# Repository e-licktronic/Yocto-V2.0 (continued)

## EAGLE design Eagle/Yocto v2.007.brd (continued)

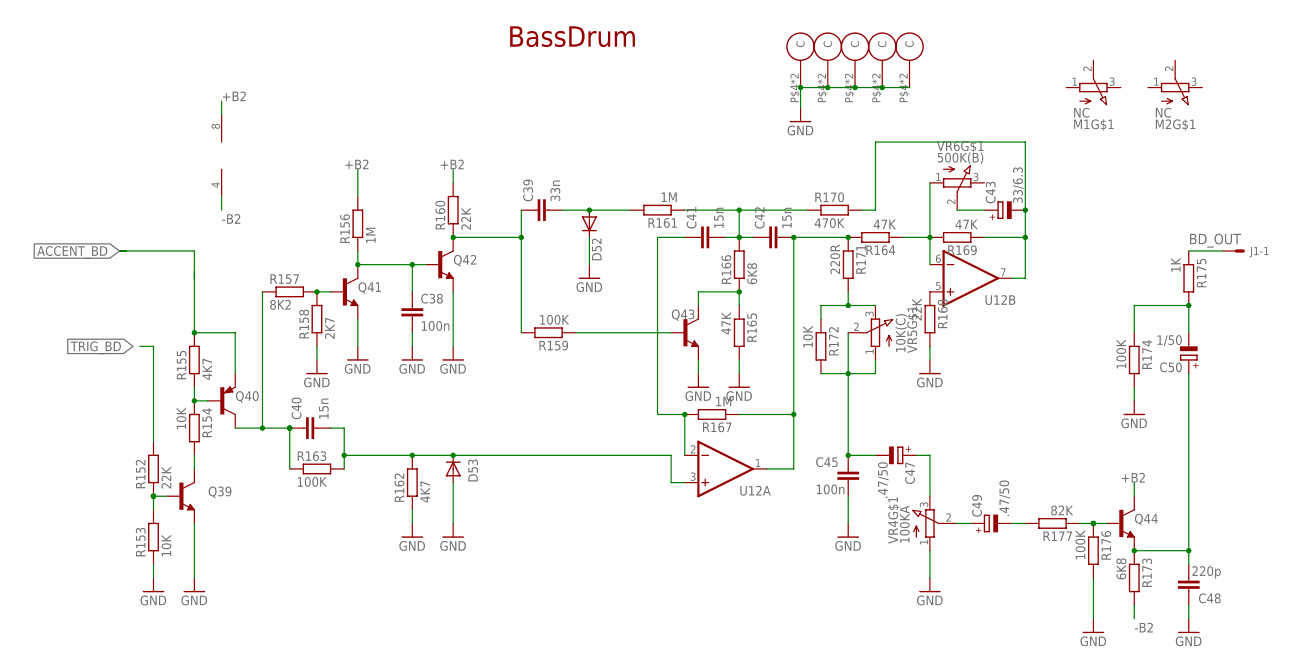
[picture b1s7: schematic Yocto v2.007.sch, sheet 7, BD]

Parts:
C38, C45: 100n; C050-025X075
C39: 33n; C050-025X075
C40, C41, C42: 15n; C050-025X075
C43: 33/6.3; E2,5-5
C47, C49: .47/50; E2,5-5
C48: 220p; C025-025X050
C50: 1/50; E2,5-5
D52, D53: 1N4148DO35-7; DO35-7
J1: 22-27-2041-04; 6410-04
M1, M2: NC; R0903N
Q39, Q41, Q42, Q43, Q44: 2SC945; TO-92-ECB-PERSO
Q40: 2SA733; TO-92-ECB-MARKED
R152: 22K; 0207/7
R153, R154: 10K; 0207/7
R155, R162: 4K7; 0207/5V
R156, R161, R167: 1M; 0207/5V
R157: 8K2; 0207/5V
R158: 2K7; 0207/5V
R159, R163, R174: 100K; 0207/5V
R160, R168: 22K; 0207/5V
R164: 47K; 0207/7
R165, R169: 47K; 0207/5V
R166, R173: 6K8; 0207/5V
R170: 470K; 0207/7
R171: 220R; 0207/5V
R172: 10K; 0207/5V
R175: 1K; 0207/5V
R176: 100K; 0207/7
R177: 82K; 0207/5V
U12: µPC4558CA; DIL08
VR4: 100KA; R0903N
VR5: 10K(C); R0903N
VR6: 500K(B); R0903N

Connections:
+B2: Q44.C, R156.2, R160.2, U12.8 (V+); also elsewhere on the board
-B2: R173.2, U12.4 (V-); also elsewhere on the board
ACCENT_BD: Q40.E, R155.2; also elsewhere on the board
BD_OUT: J1.1, R175.1
C1: C49.-, R177.2
GND: C38.2, C45.2, C48.1, D52.C, D53.A, M1.P$4 (C), M1.P$5 (C), M2.P$4 (C), M2.P$5 (C), Q39.E, Q41.E, Q42.E, Q43.E, R153.1, R158.1, R162.1, R165.2, R168.2, R174.2, R176.2, VR4.1 (A), VR4.P$4 (C), VR4.P$5 (C), VR5.P$4 (C), VR5.P$5 (C), VR6.P$4 (C), VR6.P$5 (C); also elsewhere on the board
unnamed: C38.1, Q41.C, Q42.B, R156.1
unnamed: Q40.B, R154.1, R155.1
unnamed: Q39.C, R154.2
unnamed: C39.1, Q42.C, R159.2, R160.1
unnamed: C40.1, Q40.C, R157.1, R163.1
unnamed: C40.2, D53.C, R162.2, R163.2, U12.3 (+IN)
unnamed: Q43.B, R159.1
unnamed: C41.2, C42.1, R161.1, R166.2, R170.1
unnamed: C41.1, R167.2, U12.2 (-IN)
unnamed: C42.2, R164.2, R167.1, R171.1, U12.1 (OUT)
unnamed: C45.1, C47.-, R172.2, VR5.1 (A), VR5.2 (S)
unnamed: R171.2, R172.1, VR5.3 (E)
unnamed: R164.1, R169.2, U12.6 (-IN), VR6.1 (A)
unnamed: C43.-, R169.1, R170.2, U12.7 (OUT)
unnamed: Q44.B, R176.1, R177.1
unnamed: C48.2, C50.+, Q44.E, R173.1
unnamed: C50.-, R174.1, R175.2
unnamed: C47.+, VR4.3 (E)
unnamed: C49.+, VR4.2 (S)
unnamed: C39.2, D52.A, R161.2
unnamed: C43.+, VR6.2 (S)
unnamed: R168.1, U12.5 (+IN)
unnamed: Q41.B, R157.2, R158.2
unnamed: Q43.C, R165.1, R166.1
unnamed: Q39.B, R152.1, R153.2
TRIG_BD: R152.2; also elsewhere on the board

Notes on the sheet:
BassDrum

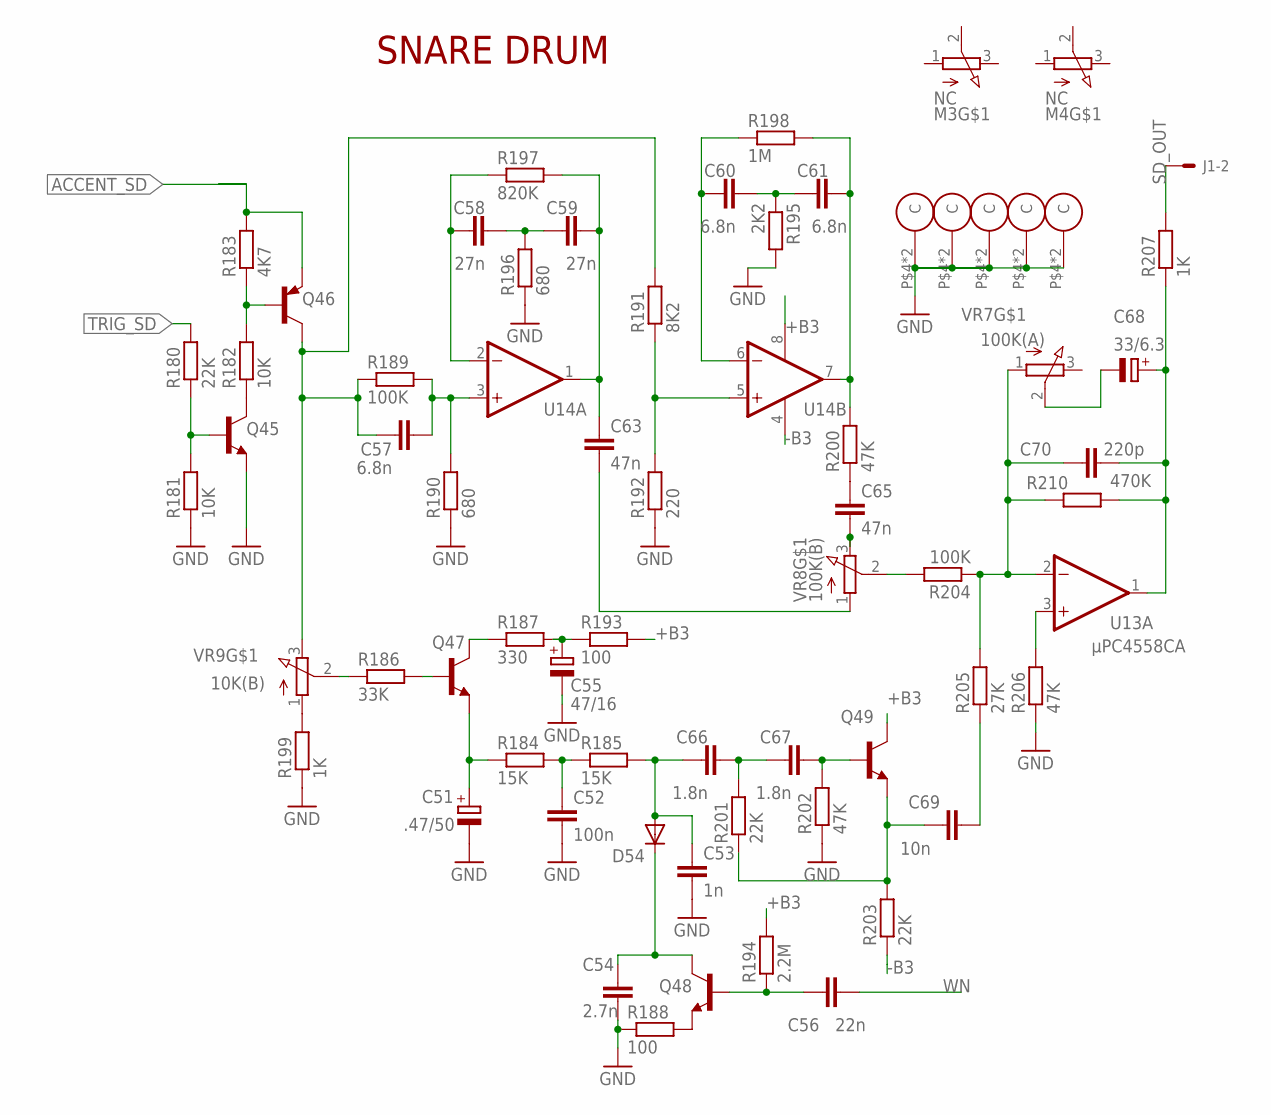
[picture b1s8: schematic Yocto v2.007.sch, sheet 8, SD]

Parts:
C51: .47/50; E2-5
C52: 100n; C050-025X075
C53: 1n; C050-025X075
C54: 2.7n; C050-025X075
C55: 47/16; E2-5
C56: 22n; C050-025X075
C57, C60, C61: 6.8n; C050-025X075
C58, C59: 27n; C050-025X075
C63, C65: 47n; C050-025X075
C66, C67: 1.8n; C050-025X075
C68: 33/6.3; E2-5
C69: 10n; C050-025X075
C70: 220p; C025-025X050
D54: 1N4148; DO35-7C
J1: 22-27-2041-04; 6410-04
M3, M4: NC; R0903N
Q45, Q47, Q48, Q49: 2SC945; TO-92-ECB-PERSO
Q46: 2SA733; TO-92-ECB-MARKED
R180, R201, R203: 22K; 0207/7
R181, R182: 10K; 0207/7
R183: 4K7; 0207/7
R184, R185: 15K; 0207/7
R186: 33K; 0207/7
R187: 330; 0207/7
R188, R193: 100; 0207/7
R189, R204: 100K; 0207/7
R190, R196: 680; 0207/7
R191: 8K2; 0207/7
R192: 220; 0207/7
R194: 2.2M; 0207/7
R195: 2K2; 0207/7
R197: 820K; 0207/7
R198: 1M; 0207/7
R199, R207: 1K; 0207/7
R200, R202, R206: 47K; 0207/7
R205: 27K; 0207/7
R210: 470K; 0207/7
U13, U14: µPC4558CA; DIL08
VR7: 100K(A); R0903N
VR8: 100K(B); R0903N
VR9: 10K(B); R0903N

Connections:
+B3: Q49.C, R193.2, R194.2, U14.8 (V+); also elsewhere on the board
-B3: R203.1, U14.4 (V-); also elsewhere on the board
ACCENT_SD: Q46.E, R183.2; also elsewhere on the board
GND: C51.-, C52.2, C53.2, C54.2, C55.-, M3.P$4 (C), M3.P$5 (C), M4.P$4 (C), M4.P$5 (C), Q45.E, R181.1, R188.1, R190.1, R192.1, R195.2, R196.1, R199.1, R202.1, R206.1, VR7.P$4 (C), VR7.P$5 (C), VR8.P$4 (C), VR8.P$5 (C), VR9.P$4 (C), VR9.P$5 (C); also elsewhere on the board
unnamed: Q45.B, R180.1, R181.2
unnamed: Q46.B, R182.2, R183.1
unnamed: Q45.C, R182.1
unnamed: C57.2, R189.2, R190.2, U14.3 (+IN)
unnamed: C57.1, Q46.C, R189.1, R191.2, VR9.3 (E)
unnamed: C58.1, R197.1, U14.2 (-IN)
unnamed: C59.2, C63.1, R197.2, U14.1 (OUT)
unnamed: C58.2, C59.1, R196.2
unnamed: C61.2, R198.2, R200.2, U14.7 (OUT)
unnamed: C60.2, C61.1, R195.1
unnamed: R191.1, R192.2, U14.5 (+IN)
unnamed: C63.2, VR8.1 (A)
unnamed: C65.1, R200.1
unnamed: R199.2, VR9.1 (A)
unnamed: C52.1, R184.2, R185.1
unnamed: R186.1, VR9.2 (S)
unnamed: Q47.B, R186.2
unnamed: Q47.C, R187.1
unnamed: C55.+, R187.2, R193.1
unnamed: C51.+, Q47.E, R184.1
unnamed: C53.1, C66.1, D54.A, R185.2
unnamed: C66.2, C67.1, R201.2
unnamed: C67.2, Q49.B, R202.2
unnamed: C69.1, Q49.E, R201.1, R203.2
unnamed: Q48.E, R188.2
unnamed: C54.1, D54.C, Q48.C
unnamed: C56.1, Q48.B, R194.1
unnamed: R204.2, VR8.2 (S)
unnamed: C70.1, R204.1, R205.2, R210.1, U13.2 (-IN), VR7.1 (A)
unnamed: C69.2, R205.1
unnamed: R206.2, U13.3 (+IN)
unnamed: C65.2, VR8.3 (E)
unnamed: C68.+, C70.2, R207.1, R210.2, U13.1 (OUT)
unnamed: C68.-, VR7.2 (S)
unnamed: C60.1, R198.1, U14.6 (-IN)
SD_OUT: J1.2, R207.2
TRIG_SD: R180.2; also elsewhere on the board
WN: C56.2; also elsewhere on the board

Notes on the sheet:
SNARE DRUM

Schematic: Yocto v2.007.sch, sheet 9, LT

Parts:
C71, C74, C77, C81: 47n; C050-025X075
C72: 39n; C050-025X075
C73: 6.8n; C050-025X075
C75: 18n; C050-025X075
C76: 56n; C050-025X075
C78: 12n; C050-025X075
C82: 33/6.3; E2-5
C83: 1n; C050-025X075
D55, D56: 1N4148; DO35-7C
D80, D81: 1N34; DO35-7C
J1: 22-27-2041-04; 6410-04
M5, M6: NC; R0903N
Q50, Q52: 2SC945; TO-92-ECB-PERSO
Q51: 2SA733; TO-92-ECB-MARKED
R211, R222, R223, R226: 22K; 0207/7
R212, R213: 10K; 0207/7
R214, R215, R219, R221, R225: 4K7; 0207/7
R216: 15K; 0207/7
R217: 3K3; 0207/7
R218: 2M2; 0207/7
R220, R227, R229: 33K; 0207/7
R224: 1K5; 0207/7
R228, R230: 820K; 0207/7
R231, R238: 1K; 0207/7
R232, R233: 100K; 0207/7
R234: 47K; 0207/7
R235: 470K; 0207/7
SW8: MSS42_SW_4PDT; MSS42_SW_SLIDE
U13, U15: µPC4558CA; DIL08
VR10: 100KA; R0903N
VR11: 500R; R0903N

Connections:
+B3: U13.8 (V+); also elsewhere on the board
+B4: R221.1, U15.8 (V+); also elsewhere on the board
-B3: U13.4 (V-); also elsewhere on the board
-B4: U15.4 (V-); also elsewhere on the board
ACCENT_LT: Q51.E, R214.2; also elsewhere on the board
GND: C72.2, C75.2, D56.A, M5.P$4 (C), M5.P$5 (C), M6.P$4 (C), M6.P$5 (C), Q50.E, Q52.E, R212.1, R215.1, R217.2, R223.2, R225.1, R234.2, SW8.2A (S), SW8.2B (S), SW8.P$1 (GND), SW8.P$2 (GND), SW8.P$3 (GND), SW8.P$4 (GND), U15.3 (+IN), VR10.P$4 (C), VR10.P$5 (C), VR11.3 (E), VR11.P$4 (C), VR11.P$5 (C); also elsewhere on the board
LT_OUT: J1.3, R238.1
unnamed: Q51.B, R213.2, R214.1
unnamed: Q50.C, R213.1
unnamed: Q50.B, R211.1, R212.2
unnamed: C73.1, Q51.C, R215.2, R219.2
unnamed: D55.A, R219.1
unnamed: C73.2, D56.C, R226.2
unnamed: C76.2, C78.1, D80.A, D81.C, R230.1, R231.2, SW8.1C (O)
unnamed: C76.1, R228.2, U15.6 (-IN)
unnamed: C77.1, C78.2, R228.1, R229.2, U15.7 (OUT)
unnamed: D80.C, D81.A, VR11.1 (A)
unnamed: R231.1, VR11.2 (S)
unnamed: R227.2, R229.1, U15.2 (-IN)
unnamed: R227.1, R230.2, R233.2, U15.1 (OUT)
unnamed: C81.1, R232.1, R233.1
unnamed: C81.2, C83.1, R235.2, U13.6 (-IN), VR10.1 (A)
unnamed: C82.-, VR10.2 (S)
unnamed: C82.+, C83.2, R235.1, R238.2, U13.7 (OUT)
unnamed: C74.1, Q52.C, R221.2
unnamed: C75.1, R222.1, SW8.1A (O)
unnamed: Q52.B, R220.2
unnamed: C71.2, R216.2, R217.1
unnamed: C72.1, D55.C, R218.1
unnamed: C77.2, SW8.CC
unnamed: R232.2, SW8.CA
unnamed: C74.2, R222.2, R223.1
unnamed: R224.2, R225.2, R226.1, U15.5 (+IN)
unnamed: R234.1, U13.5 (+IN)
unnamed: R224.1, SW8.CB
unnamed: C71.1, R218.2, R220.1
PN: R216.1; also elsewhere on the board
TRIG_LT: R211.2; also elsewhere on the board

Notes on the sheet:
LOW TOM LOW CONGA

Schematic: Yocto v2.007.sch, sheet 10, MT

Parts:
C84: 47n; C050-025X075
C85, C87: 33n; C050-025X075
C86: 2.7n; C050-025X075
C88: 15n; C050-025X075
C89: 8.2n; C050-025X075
C90, C91: 27n; C050-025X075
C92: 12n; C050-025X075
C95: 33/6.3; E2-5
C96: 39n; C050-025X075
C97: 1n; C050-025X075
D57, D58: 1N4148; DO35-7C
D82, D83: 1N34; DO35-7C
J1: 22-27-2041-04; 6410-04
M7, M8: NC; R0903N
Q53, Q55: 2SC945; TO-92-ECB-PERSO
Q54: 2SA733; TO-92-ECB-MARKED
R239, R260: 1K; 0207/7
R240, R249, R250, R255: 22K; 0207/7
R241, R242: 10K; 0207/7
R243, R244, R251, R252: 4K7; 0207/7
R245: 15K; 0207/7
R246: 3K3; 0207/7
R247: 2M2; 0207/7
R248, R256, R258: 33K; 0207/7
R253: 2K2; 0207/7
R254: 6K8; 0207/7
R257, R259: 820K; 0207/7
R261, R262: 100K; 0207/7
R263: 47K; 0207/7
R266: 470K; 0207/7
SW9: MSS42_SW_4PDT; MSS42_SW_SLIDE
U16, U17: µPC4558CA; DIL08
VR12: 100KA; R0903N
VR13: 500R; R0903N

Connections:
+B5: R252.1, U16.8 (V+), U17.8 (V+); also elsewhere on the board
-B5: U16.4 (V-), U17.4 (V-); also elsewhere on the board
ACCENT_MT: Q54.E, R243.2; also elsewhere on the board
GND: C85.2, C88.2, D58.A, M7.P$4 (C), M7.P$5 (C), M8.P$4 (C), M8.P$5 (C), Q53.E, Q55.E, R241.1, R246.2, R249.2, R251.1, R254.1, R263.2, SW9.2A (S), SW9.2B (S), SW9.P$1 (GND), SW9.P$2 (GND), SW9.P$3 (GND), SW9.P$4 (GND), U17.3 (+IN), VR12.P$4 (C), VR12.P$5 (C), VR13.3 (E), VR13.P$4 (C), VR13.P$5 (C); also elsewhere on the board
MT_OUT: J1.4, R239.1
unnamed: Q54.B, R242.2, R243.1
unnamed: Q53.C, R242.1
unnamed: Q53.B, R240.1, R241.2
unnamed: C86.1, Q54.C, R244.2, R251.2
unnamed: D57.A, R244.1
unnamed: C86.2, D58.C, R255.2
unnamed: C90.2, C92.1, D82.A, D83.C, R259.1, R260.2, SW9.1C (O), SW9.1D (O)
unnamed: C89.2, C90.1, R257.2, U17.6 (-IN)
unnamed: C91.1, C92.2, R257.1, R258.2, U17.7 (OUT)
unnamed: D82.C, D83.A, VR13.1 (A)
unnamed: R260.1, VR13.2 (S)
unnamed: R256.2, R258.1, U17.2 (-IN)
unnamed: R256.1, R259.2, R262.2, U17.1 (OUT)
unnamed: C96.1, R261.1, R262.1
unnamed: C96.2, C97.1, R266.2, U16.2 (-IN), VR12.1 (A)
unnamed: C95.-, VR12.2 (S)
unnamed: C95.+, C97.2, R239.2, R266.1, U16.1 (OUT)
unnamed: C87.1, Q55.C, R252.2
unnamed: C88.1, R250.2, SW9.1A (O)
unnamed: Q55.B, R248.2
unnamed: C84.2, R245.2, R246.1
unnamed: C84.1, R247.2, R248.1
unnamed: C85.1, D57.C, R247.1
unnamed: C91.2, SW9.CD
unnamed: R261.2, SW9.CA
unnamed: C87.2, R249.1, R250.1
unnamed: R263.1, U16.3 (+IN)
unnamed: R253.1, SW9.CB
unnamed: R253.2, R254.2, R255.1, U17.5 (+IN)
unnamed: C89.1, SW9.CC
PN: R245.1; also elsewhere on the board
TRIG_MT: R240.2; also elsewhere on the board

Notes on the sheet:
MID TOM MID CONGA

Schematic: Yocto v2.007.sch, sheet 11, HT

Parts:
C98: 47n; C050-025X075
C99: 2.7n; C050-025X075
C100, C108: 33n; C050-025X075
C101, C103: 27n; C050-025X075
C102: 10n; C050-025X075
C104: 22n; C050-025X075
C105: 5.6n; C050-025X075
C109: 33/6.3; E2-5
C110: 1n; C050-025X075
D59, D60: 1N4148; DO35-7C
D84, D85: 1N34; DO35-7C
J3: 22-27-2041-04; 6410-04
M9, M10: NC; R0903N
Q56, Q58: 2SC945; TO-92-ECB-PERSO
Q57: 2SA733; TO-92-ECB-MARKED
R267, R277, R278, R282: 22K; 0207/7
R268, R271: 10K; 0207/7
R269, R270, R274, R279: 4K7; 0207/7
R272: 3K3; 0207/7
R273: 15K; 0207/7
R275, R283, R285: 33K; 0207/7
R276: 2M2; 0207/7
R280: 1K5; 0207/7
R281: 5K6; 0207/7
R284, R286: 820K; 0207/7
R287, R294: 1K; 0207/7
R288, R289: 100K; 0207/7
R290: 47K; 0207/7
R291: 470K; 0207/7
SW10: MSS42_SW_4PDT; MSS42_SW_SLIDE
U16, U18: µPC4558CA; DIL08
VR14: 100KA; R0903N
VR15: 500R; R0903N

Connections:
+B6: R279.1, U18.8 (V+); also elsewhere on the board
-B6: U18.4 (V-); also elsewhere on the board
ACCENT_HT: Q57.E, R269.2; also elsewhere on the board
GND: C100.2, C102.2, D60.A, M9.P$4 (C), M9.P$5 (C), M10.P$4 (C), M10.P$5 (C), Q56.E, Q58.E, R270.1, R271.1, R272.2, R277.2, R281.1, R290.2, SW10.2B (S), SW10.2C (S), SW10.P$1 (GND), SW10.P$2 (GND), SW10.P$3 (GND), SW10.P$4 (GND), U18.3 (+IN), VR14.P$4 (C), VR14.P$5 (C), VR15.3 (E), VR15.P$4 (C), VR15.P$5 (C); also elsewhere on the board
HT_OUT: J3.1, R294.1
unnamed: Q57.B, R268.2, R269.1
unnamed: Q56.C, R268.1
unnamed: Q56.B, R267.1, R271.2
unnamed: C99.1, Q57.C, R270.2, R274.2
unnamed: D59.A, R274.1
unnamed: C99.2, D60.C, R282.2
unnamed: C103.2, C105.1, D84.A, D85.C, R286.1, R287.2, SW10.1A (O)
unnamed: C103.1, R284.2, U18.6 (-IN)
unnamed: C104.1, C105.2, R284.1, R285.2, U18.7 (OUT)
unnamed: D84.C, D85.A, VR15.1 (A)
unnamed: R287.1, VR15.2 (S)
unnamed: R283.2, R285.1, U18.2 (-IN)
unnamed: R283.1, R286.2, R289.2, U18.1 (OUT)
unnamed: C108.1, R288.1, R289.1
unnamed: C108.2, C110.1, R291.2, U16.6 (-IN), VR14.1 (A)
unnamed: C109.-, VR14.2 (S)
unnamed: C109.+, C110.2, R291.1, R294.2, U16.7 (OUT)
unnamed: C101.1, Q58.C, R279.2
unnamed: C102.1, R278.2, SW10.1B (O)
unnamed: Q58.B, R275.2
unnamed: C98.2, R272.1, R273.2
unnamed: C98.1, R275.1, R276.2
unnamed: C100.1, D59.C, R276.1
unnamed: C104.2, SW10.CA
unnamed: R288.2, SW10.CB
unnamed: C101.2, R277.1, R278.1
unnamed: R290.1, U16.5 (+IN)
unnamed: R280.2, R281.2, R282.1, U18.5 (+IN)
unnamed: R280.1, SW10.CC
PN: R273.1; also elsewhere on the board
TRIG_HT: R267.2; also elsewhere on the board

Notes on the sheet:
HI TOM HI CONGA

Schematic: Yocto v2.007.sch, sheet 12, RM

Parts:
C24: .47/50; E2-5
C111, C125: 10n; C050-025X075
C112: 22n; C050-025X075
C113: 47n; C050-025X075
C114: 1n; C050-025X075
C115, C116, C121, C122: 4.7n; C050-025X075
C117, C118, C119: 2.2n; C050-025X075
C120: 10/16; E2-5
C126: 33/6.3; E2-5
C153: 22p; C025-025X050
D61, D62, D63, D64: 1N4148; DO35-7C
J3: 22-27-2041-04; 6410-04
M11: NC; R0903N
Q59, Q61, Q62, Q63: 2SC945; TO-92-ECB-PERSO
Q60: 2SA733; TO-92-ECB-MARKED
Q74: 2SK30; TO-92-MARKED_FET
R107, R295, R312: 1K; 0207/7
R108, R298, R302, R303, R311, R317, R322, R326: 10K; 0207/7
R297, R300, R306, R320, R323: 22K; 0207/7
R299: 4K7; 0207/7
R301, R304, R331: 47K; 0207/7
R305, R316: 1M; 0207/7
R307: 100K; 0207/7
R308: 820K; 0207/7
R309, R310, R314: 33K; 0207/7
R313: 390K; 0207/7
R315: 5K6; 0207/7
R318, R319, R324: 220K; 0207/7
R321: 2M2; 0207/7
R325: 330K; 0207/7
R327, R330: 470K; 0207/7
SW11: MSS42_SW_4PDT; MSS42_SW_SLIDE
U19, U20, U21: µPC4558CA; DIL08
VR16: 100KA; R0903N

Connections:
+B7: Q63.C, R321.1, U20.8 (V+); also elsewhere on the board
-B7: Q61.E, R304.1, R323.2, U20.4 (V-); also elsewhere on the board
ACCENT_RM: Q60.E, R299.2; also elsewhere on the board
GND: C24.-, C113.2, M11.P$4 (C), M11.P$5 (C), Q59.E, Q62.E, R300.1, R302.1, R303.1, R305.1, R306.2, R307.1, R311.2, R312.2, R315.1, R317.2, R325.2, R331.1, SW11.P$1 (GND), SW11.P$2 (GND), SW11.P$3 (GND), SW11.P$4 (GND), U20.5 (+IN), VR16.P$4 (C), VR16.P$5 (C); also elsewhere on the board
unnamed: C113.1, Q61.C, Q74.G, R305.2, R327.2
unnamed: C112.2, Q61.B, R304.2
unnamed: C118.2, SW11.1C (O)
unnamed: C24.+, R107.1, R108.2
unnamed: C153.2, Q74.D, R295.2, R327.1, R330.2, U19.1 (OUT), VR16.2 (S)
unnamed: C121.1, D63.C, Q62.C
unnamed: C114.1, D64.A, R306.1
unnamed: C120.+, Q62.B, R321.2
unnamed: C111.2, D62.A, R307.2
unnamed: R331.2, U19.3 (+IN)
unnamed: C125.1, SW11.CD
unnamed: R313.2, SW11.2C (S)
unnamed: Q60.B, R298.2, R299.1
unnamed: Q59.B, R297.1, R303.2
unnamed: Q59.C, R298.1
unnamed: D61.C, R107.2
unnamed: D63.A, R108.1
unnamed: C121.2, C122.1, R322.1
unnamed: C122.2, Q63.B, R325.1
unnamed: Q63.E, R322.2, R323.1, R324.2
unnamed: D62.C, R301.2
unnamed: R301.1, R302.2, U21.3 (+IN)
unnamed: D64.C, R310.2
unnamed: R310.1, R311.1, U20.3 (+IN)
unnamed: C117.2, C119.1, R312.1, SW11.CC
unnamed: C119.2, R308.2, U20.2 (-IN)
unnamed: C117.1, C118.1, R308.1, R314.2, U20.1 (OUT)
unnamed: R309.2, R314.1, U20.6 (-IN)
unnamed: R309.1, R313.1, R319.1, R320.2, U20.7 (OUT)
unnamed: R319.2, SW11.2D (S)
unnamed: C125.2, R326.1
unnamed: C126.+, C153.1, R326.2, R330.1, U19.2 (-IN)
unnamed: C126.-, Q74.S, VR16.1 (A)
unnamed: C115.2, C116.1, R315.2
unnamed: C116.2, R316.2, U21.2 (-IN)
unnamed: C115.1, R316.1, R318.2, U21.1 (OUT)
unnamed: C120.-, R317.1, R318.1, R320.1
unnamed: C111.1, C112.1, C114.2, D61.A, Q60.C, R300.2
unnamed: R324.1, SW11.1D (O)
RM_OUT: J3.2, R295.1
TRIG_RM: R297.2; also elsewhere on the board

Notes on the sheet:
RimShot Clave

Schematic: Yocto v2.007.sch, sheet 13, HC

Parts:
C127: 1.8n; C050-025X075
C128, C129, C152: 4.7n; C050-025X075
C130, C138: 47n; C050-025X075
C131, C151: 10n; C050-025X075
C132, C133, C141, C150: 1n; C050-025X075
C134, C137: 33n; C050-025X075
C135: 100n; C050-025X075
C136: 22n; C050-025X075
C139, C146: 18n; C050-025X075
C140: 27n; C050-025X075
C142, C149: 220p; C025-025X050
C143: 1/50; E2-5
C144: .47/50; E2-5
C145: 33/6.3; E2-5
D65, D66, D67, D68, D69, D70, D71: 1N4148; DO35-7C
J3: 22-27-2041-04; 6410-04
Q28, Q67, Q68, Q69, Q70, Q73: 2SC945; TO-92-ECB-PERSO
Q29, Q65, Q66, Q71, Q72: 2SA733; TO-92-ECB-MARKED
R103, R347, R361: 22K; 0207/7
R104, R106, R200', R333, R337, R359, R363, R374: 10K; 0207/7
R105, R351, R352, R353: 4K7; 0207/7
R296, R381, R382: 1K; 0207/7
R332, R360: 27K; 0207/7
R334, R343, R377, R378: 100K; 0207/7
R335: 6K8; 0207/7
R336, R348, R349, R350, R356: 1M; 0207/7
R338, R342, R366, R371: 15K; 0207/7
R339: 3K3; 0207/7
R340, R357, R358: 68K; 0207/7
R341, R368, R375: 470K; 0207/7
R344: 220K; 0207/7
R345: 150K; 0207/7
R346: 680; 0207/7
R354: 5K6; 0207/7
R355: 2K7; 0207/7
R362: 330K; 0207/7
R364: 2K2; 0207/7
R365, R383: 82K; 0207/7
R367: 330; 0207/7
R369: 330R; 0207/7
R370, R373, R376: 47K; 0207/7
R372: 39K; 0207/7
SW12: MSS12; MSS12_SW_SLIDE
TM3: 10K(B); CT6
U19, U21: µPC4558CA; DIL08
U22: BA6110SIL; SIL09
U23: AN6912; DIL14
VR17: 100K(A); R0903N

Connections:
+B7: U19.8 (V+), U21.8 (V+); also elsewhere on the board
+B8: Q65.E, Q68.C, Q69.C, R343.1, R363.1, R366.1, U22.9 (V+); also elsewhere on the board
-B7: U19.4 (V-), U21.4 (V-); also elsewhere on the board
-B8: D70.A, Q71.C, Q73.E, R200'.2, R347.2, R351.2, R361.2, TM3.A, U22.3, U22.5 (V-), U23.12 (V-); also elsewhere on the board
ACCENT_HC: Q29.E, R105.2; also elsewhere on the board
CPTRIG: Q29.C, SW12.2
CP_MA_OUT: J3.3, R296.1
GND: C134.2, C135.2, C138.2, C139.1, C140.1, C143.-, C144.+, C146.2, Q28.E, Q66.C, Q67.E, R104.1, R333.1, R336.1, R338.1, R340.2, R345.1, R346.1, R350.1, R353.1, R354.2, R359.1, R364.2, R365.2, R369.2, R371.1, R373.1, R381.1, R382.2, R383.1, SW12.P$4, SW12.P$5, SW12.P$6, SW12.P$7, TM3.E, U21.5 (+IN), U23.3 (V+), VR17.P$4 (C), VR17.P$5 (C); also elsewhere on the board
unnamed: Q28.B, R103.2, R104.2
unnamed: Q29.B, R105.1, R106.2
unnamed: Q28.C, R106.1
unnamed: C137.2, Q70.B, R349.1
unnamed: C139.2, D69.C, R348.2
unnamed: Q70.E, R200'.1, R369.1
unnamed: Q69.B, R360.1, SW12.1 (O)
unnamed: D68.A, D69.A, Q69.E
unnamed: C138.1, R348.1, R349.2
unnamed: C146.1, C152.1, Q70.C, R363.2
unnamed: C143.+, D68.C, R362.2
unnamed: Q71.B, R362.1, R364.1, R370.2
unnamed: R370.1, TM3.S
unnamed: C129.2, C136.1, R334.2, R342.1, U21.7 (OUT)
unnamed: C137.1, R342.2, R346.2
unnamed: C127.2, C128.2, C129.1, R332.2, R333.2
unnamed: C128.1, R334.1, U21.6 (-IN)
unnamed: C136.2, R372.2
unnamed: R372.1, R382.1, U22.2 (-IN)
unnamed: C152.2, R376.1
unnamed: C150.2, R378.1
unnamed: R383.2, U22.6 (OUT), U22.7 (IN1)
unnamed: C150.1, U22.8 (OUT1)
unnamed: R352.1, R353.2, U23.6 (-IN), U23.11 (+IN)
unnamed: D71.A, R365.1, U23.13 (OUT)
unnamed: C144.-, D71.C, R356.1, R367.1
unnamed: Q72.B, R368.1, R371.2
unnamed: Q71.E, Q72.E, R366.2
unnamed: Q72.C, R374.2
unnamed: Q73.C, R367.2, R368.2
unnamed: C142.2, R356.2, U23.5 (+IN)
unnamed: C141.1, R355.2, U23.1 (OUT), U23.10 (-IN)
unnamed: Q73.B, R357.1, R358.2
unnamed: C141.2, D70.C, R357.2
unnamed: C142.1, R358.1, R359.2, U23.2 (OUT)
unnamed: R351.1, R352.2, U23.9 (+IN)
unnamed: R360.2, R361.1, U23.8 (-IN)
unnamed: C140.2, R350.2, U23.7 (+IN), U23.14 (OUT)
unnamed: R354.1, R355.1, U23.4 (-IN)
unnamed: Q67.B, R344.2
unnamed: D65.A, Q65.C
unnamed: C135.1, D67.C, R344.1, R345.2
unnamed: C134.1, D66.C, Q66.B, R341.2
unnamed: Q66.E, R337.2
unnamed: C131.2, D65.C, R337.1
unnamed: C131.1, C132.2, R338.2
unnamed: C132.1, C133.2, R339.1
unnamed: C133.1, Q68.B, R340.1
unnamed: C151.2, Q68.E, R339.2, R347.1
unnamed: C130.2, Q65.B, R336.2
unnamed: C130.1, R335.2
unnamed: C151.1, R377.2
unnamed: R373.2, U19.5 (+IN)
unnamed: C149.2, R375.2, R376.2, R377.1, R378.2, U19.6 (-IN), VR17.1 (A)
unnamed: C145.+, C149.1, R296.2, R375.1, U19.7 (OUT)
unnamed: C145.-, VR17.2 (S)
unnamed: D67.A, SW12.3 (S)
unnamed: D66.A, Q67.C, R341.1, R343.2
unnamed: R381.2, U22.1 (+IN)
unnamed: R374.1, U22.4 (C)
TRIG_HC: R103.1; also elsewhere on the board
WN: C127.1, R332.1, R335.1; also elsewhere on the board

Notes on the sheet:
HANDCLAP / MARACAS

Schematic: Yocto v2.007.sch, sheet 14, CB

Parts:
C9*: .47/50; E2-5
C28*: 10n; C050-025X075
C29*: 3.3n; C050-025X075
C30*, C31*: 2.2n; C050-025X075
C32*, C33*: 10/16; E2-5
C34*, C75*: 1/50; E2-5
C76*: 22n; C050-025X075
D2*, D3*, D4*: 1N4148; DO35-7C
J3: 22-27-2041-04; 6410-04
M12, M13: NC; R0903N
Q1*, Q14*, Q15*: 2SC945; TO-92-ECB-PERSO
Q5*: 2SA733; TO-92-ECB-MARKED
R4*, R9*, R117*: 22K; 0207/7
R5*, R26*, R27*: 10K; 0207/7
R14*: 4K7; 0207/7
R24*, R63*, R65*: 2K2; 0207/7
R25*, R30*, R32*: 470K; 0207/7
R28*, R29*: 100K; 0207/7
R31*, R33*: 100R; 0207/7
R62*, R64*, R82*: 33K; 0207/7
R116*: 8K2; 0207/7
R122*, R163*: 1K; 0207/7
U2: µPC4558CA; DIL08
VR5*: 5KA; R0903N

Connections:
+B1*: R30*.2, R32*.2, U2.8 (V+); also elsewhere on the board
-B1*: U2.4 (V-); also elsewhere on the board
ACCENT_CB: Q5*.E, R14*.2; also elsewhere on the board
CB_OUT: J3.4, R163*.2
GND: C9*.-, C34*.-, M12.P$4 (C), M12.P$5 (C), M13.P$4 (C), M13.P$5 (C), Q1*.E, R5*.1, R24*.1, R31*.1, R33*.1, R63*.2, R65*.2, R117*.2, U2.5 (+IN), VR5*.1 (A), VR5*.P$4 (C), VR5*.P$5 (C); also elsewhere on the board
unnamed: Q5*.B, R9*.2, R14*.1
unnamed: Q1*.C, R9*.1
unnamed: Q1*.B, R4*.1, R5*.2
unnamed: C9*.+, D2*.C, R28*.2, R29*.2, R82*.1
unnamed: Q15*.E, R31*.2
unnamed: C32*.+, Q15*.B, R30*.1
unnamed: D3*.C, Q15*.C
unnamed: D3*.A, R26*.2, R28*.1
unnamed: Q14*.E, R33*.2
unnamed: C33*.+, Q14*.B, R32*.1
unnamed: D4*.C, Q14*.C
unnamed: D4*.A, R27*.2, R29*.1
unnamed: C30*.1, R26*.1
unnamed: C31*.1, R27*.1
unnamed: C28*.1, C29*.1, C30*.2, C31*.2, R24*.2
unnamed: C29*.2, C75*.-, R25*.1, U2.7 (OUT)
unnamed: C28*.2, R25*.2, U2.6 (-IN)
unnamed: R163*.1, U2.1 (OUT), U2.2 (-IN)
unnamed: C76*.2, R117*.1, U2.3 (+IN)
unnamed: C76*.1, VR5*.2 (S)
unnamed: R116*.2, VR5*.3 (E)
unnamed: C75*.+, R116*.1
unnamed: C32*.-, R62*.2, R63*.1
unnamed: C33*.-, R64*.2, R65*.1
unnamed: C34*.+, R82*.2
unnamed: Q5*.C, R122*.2
unnamed: D2*.A, R122*.1
TP6: R62*.1; also elsewhere on the board
TP7: R64*.1; also elsewhere on the board
TRIG_CB: R4*.2; also elsewhere on the board

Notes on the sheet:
Cowbell

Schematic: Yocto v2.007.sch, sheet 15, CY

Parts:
C1*, C4*, C5*: 18n; C050-025X075
C2*, C3*, C55*, C56*, C58*, C90*: 10n; C050-025X075
C6*, C42*, C44*, C46*: 22n; C050-025X075
C10*, C15*, C16*, C49*, C57*: 3.3n; C050-025X075
C11*, C51*, C52*, C53*, C54*: 1n; C050-025X075
C12*: 100/6.3; E2-5
C13*, C14*: 6.8n; C050-025X075
C35*: 47/16; E2-5
C36*, C43*, C47*, C48*, C50*, C59*: 1.5n; C050-025X075
C37*, C45*: 2.2/50; E2-5
C38*, C40*, C41*: 1/50; E2-5
C39*: .47/50; E2-5
C77*: 220p; C025-025X050
C78*: 33/6.3; E2-5
D5*, D6*, D7*, D8*, D11*, D12*: 1N4148; DO35-7C
J4: 22-27-2041-04; 6410-04
Q2*, Q9*, Q16*, Q17*, Q18*, Q19*, Q20*, Q25*: 2SC945; TO-92-ECB-PERSO
Q6*: 2SA733; TO-92-ECB-MARKED
R3*, R55*, R83*, R87*, R104*, R111*, R112*, R119*, R124*, R126*: 22K; 0207/7
R6*, R61*, R84*, R89*, R120*, R121*: 10K; 0207/7
R10*, R15*: 4K7; 0207/7
R35*, R37*, R39*, R46*, R48*, R50*: 120K; 0207/7
R40*, R41*: 560K; 0207/7
R42*: 680K; 0207/7
R43*: 220K; 0207/7
R44*: 150K; 0207/7
R45*, R123*: 100K; 0207/7
R52*, R88*, R90*, R91*, R92*, R105*: 33K; 0207/7
R53*, R166*: 1K; 0207/7
R56*, R58*: 560R; 0207/7
R57*, R59*, R127*: 82K; 0207/7
R60*: 5K6; 0207/7
R85*, R86*, R95*, R98*, R101*: 100R; 0207/7
R93*, R128*: 470K; 0207/7
R94*, R110*, R114*, R115*: 39K; 0207/7
R96*, R97*, R99*, R100*, R102*, R103*: 1M; 0207/7
R106*: 6K8; 0207/7
R107*, R108*, R109*, R113*: 18K; 0207/7
R118*: 47K; 0207/7
R125*: 2K2; 0207/7
R129*: 15K; 0207/7
TM1*, TM2*: 220KB; CT6
TP6, TP7: TPB0,8; B0,8
U3, U5, U6: µPC4558CA; DIL08
U4: 4584N; DIL14
VR2*: 2MB; R1212N
VR4*: 20KB; R0903N
VR6*: 100KA; R0903N

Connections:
+B1*: Q20*.C, Q25*.C, R86*.1, R96*.2, R100*.2, R102*.2, U5.8 (V+), U6.8 (V+); also elsewhere on the board
+B4*: Q9*.C, R61*.2, U3.8 (V+); also elsewhere on the board
-B1*: R126*.2, U5.4 (V-), U6.4 (V-); also elsewhere on the board
-B4*: U3.4 (V-); also elsewhere on the board
ACCENT_CY: Q6*.E, R15*.2; also elsewhere on the board
CY_OUT: J4.1, R166*.2
GND: C1*.1, C2*.1, C3*.1, C4*.1, C5*.1, C6*.1, C12*.-, C35*.-, C36*.2, C37*.-, C38*.-, C39*.-, C40*.-, C41*.-, C43*.1, C45*.-, C47*.2, C50*.1, C57*.2, Q2*.E, R6*.1, R53*.1, R56*.1, R58*.1, R60*.1, R83*.1, R89*.1, R95*.2, R98*.1, R101*.1, R106*.2, R109*.2, R111*.1, R113*.2, R115*.1, R118*.1, R127*.2, U3.3 (+IN), U3.5 (+IN), U4.7 (VSS), U6.3 (+IN), VR2*.1 (A), VR2*.P$4 (C), VR2*.P$5 (C), VR4*.2 (S), VR4*.P$4 (C), VR4*.P$5 (C), VR6*.P$4 (C), VR6*.P$5 (C); also elsewhere on the board
unnamed: C78*.+, VR6*.2 (S), VR6*.3 (E)
unnamed: R102*.1, R103*.2
unnamed: C58*.1, Q25*.E, R124*.2, R126*.1
unnamed: R93*.1, VR2*.2 (S), VR2*.3 (E)
unnamed: R99*.2, R100*.1
unnamed: R96*.1, R97*.2
unnamed: R118*.2, U6.5 (+IN)
unnamed: C1*.2, R40*.2, U4.5 (I)
unnamed: C2*.2, R41*.1, U4.3 (I)
unnamed: C3*.2, R42*.2, U4.1 (I)
unnamed: C4*.2, R43*.2, U4.9 (I)
unnamed: C5*.2, TM2*.E, U4.11 (I)
unnamed: C6*.2, TM1*.E, U4.13 (I)
unnamed: R35*.2, R40*.1, U4.6 (O)
unnamed: R37*.1, R41*.2, U4.4 (O)
unnamed: R43*.1, R46*.2, U4.8 (O)
unnamed: R45*.1, TM2*.S
unnamed: R44*.1, TM1*.S
unnamed: C12*.+, Q9*.E, U4.14 (VDD)
unnamed: Q9*.B, R60*.2, R61*.1
unnamed: R39*.1, R42*.1, U4.2 (O)
unnamed: C50*.2, C51*.1, D11*.A, R90*.1, R91*.2
unnamed: Q16*.E, R95*.1
unnamed: U6.1 (OUT), U6.2 (-IN)
unnamed: C10*.1, C11*.1, R35*.1, R37*.2, R39*.2, R46*.1, R48*.2, R50*.1, R53*.2
unnamed: C11*.2, R55*.1
unnamed: C15*.1, R55*.2, R59*.1, U3.6 (-IN)
unnamed: C44*.2, Q17*.B, R99*.1
unnamed: Q17*.E, R98*.2
unnamed: C43*.2, D11*.C, Q17*.C
unnamed: C39*.+, R88*.2, R90*.2
unnamed: C10*.2, R52*.1
unnamed: C13*.1, R52*.2, R57*.1, U3.2 (-IN)
unnamed: C14*.2, C46*.1, R57*.2, U3.1 (OUT)
unnamed: C46*.2, Q18*.B, R103*.1
unnamed: Q18*.E, R101*.2
unnamed: D12*.C, Q18*.C
unnamed: C48*.1, D12*.A, R104*.1
unnamed: C40*.+, D7*.C, R88*.1
unnamed: C35*.+, R85*.1, R86*.2
unnamed: Q19*.C, R85*.2
unnamed: D6*.A, D7*.A, D8*.A, Q19*.E
unnamed: Q19*.B, R84*.1
unnamed: Q6*.C, R83*.2, R84*.2
unnamed: Q6*.B, R10*.2, R15*.1
unnamed: Q2*.B, R3*.1, R6*.2
unnamed: Q2*.C, R10*.1
unnamed: C36*.1, D5*.C, Q16*.C
unnamed: C47*.1, C49*.1, D5*.A, R94*.2
unnamed: C42*.2, Q16*.B, R97*.1
unnamed: C37*.+, R87*.2
unnamed: Q20*.E, R92*.2, R105*.2
unnamed: R89*.2, R91*.1, R92*.1
unnamed: C41*.+, D8*.C, Q20*.B, R93*.2
unnamed: C49*.2, C53*.1, R106*.1
unnamed: C54*.2, R109*.1, U5.3 (+IN)
unnamed: R112*.2, R119*.1, VR4*.1 (A)
unnamed: C55*.1, R108*.2, R110*.2, U5.1 (OUT)
unnamed: C53*.2, C54*.1, R108*.1
unnamed: R110*.1, R111*.2, U5.2 (-IN)
unnamed: C55*.2, R112*.1
unnamed: R125*.1, VR4*.3 (E)
unnamed: C52*.2, R113*.1, U5.5 (+IN)
unnamed: C56*.1, R107*.2, R114*.2, U5.7 (OUT)
unnamed: C51*.2, C52*.1, R107*.1
unnamed: R114*.1, R115*.2, U5.6 (-IN)
unnamed: C77*.1, C78*.-, C90*.2, R128*.1, U6.6 (-IN)
unnamed: C77*.2, R128*.2, R166*.1, U6.7 (OUT), VR6*.1 (A)
unnamed: C56*.2, R120*.1
unnamed: R120*.2, R121*.2, R125*.2, R129*.1
unnamed: C90*.1, R119*.2, R129*.2
unnamed: C48*.2, C59*.1, R124*.1
unnamed: C59*.2, Q25*.B, R127*.1
unnamed: C58*.2, R123*.1
unnamed: C57*.1, R121*.1, R123*.2
unnamed: C15*.2, C16*.1, R58*.2
unnamed: C13*.2, C14*.1, R56*.2
unnamed: C45*.+, R104*.2, R105*.1
unnamed: C38*.+, D6*.C, R87*.1, R94*.1
TO_HH: C16*.2, C42*.1, C44*.1, R59*.2, U3.7 (OUT); also elsewhere on the board
TP6: R44*.2, R50*.2, TP6.P$1, U4.12 (O); also elsewhere on the board
TP7: R45*.2, R48*.1, TP7.P$1, U4.10 (O); also elsewhere on the board
TRIG_CY: R3*.2; also elsewhere on the board

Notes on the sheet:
Cymbal

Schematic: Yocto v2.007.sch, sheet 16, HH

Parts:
C60*: 10/16; E2-5
C61*: 47/16; E2-5
C62*, C63*: .47/50; E2-5
C64*, C65*, C66*, C68*, C69*, C70*: 1.5n; C050-025X075
C67*, C71*: 22n; C050-025X075
C72*, C73*: 1n; C050-025X075
C74*, C80*: 470p; C050-025X075
C79*, C82*: 220p; C025-025X050
C81*, C83*: 33/6.3; E2-5
D13*, D14*: 1N4148; DO35-7C
J4: 22-27-2041-04; 6410-04
M14, M15, M16: NC; R0903N
Q3*, Q4*, Q21*, Q22*, Q23*, Q24*, Q26*, Q27*, Q28*, Q29*, Q30*, Q31*: 2SC945; TO-92-ECB-PERSO
Q7*, Q8*: 2SA733; TO-92-ECB-MARKED
R1*, R2*, R11*, R12*, R13*, R131*, R154*, R156*: 22K; 0207/7
R7*, R8*, R130*, R133*, R135*: 10K; 0207/7
R16*, R17*: 4K7; 0207/7
R132*, R134*: 100K; 0207/7
R136*, R145*, R152*: 100R; 0207/7
R137*, R138*: 470R; 0207/7
R139*, R148*, R149*, R150*, R151*: 1M; 0207/7
R140*, R141*, R142*, R143*, R144*, R162*: 33K; 0207/7
R146*, R155*: 68K; 0207/7
R147*, R153*: 2K7; 0207/7
R157*, R158*: 47K; 0207/7
R159*, R161*: 470K; 0207/7
R160*: 39K; 0207/7
R169*, R172*: 1K; 0207/7
R173*: 330K; 0207/7
U7: µPC4558CA; DIL08
VR3*: 2MB; R1212N
VR7*, VR8*: 100KA; R0903N

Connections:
+B3*: Q26*.C, Q29*.C, Q31*.C, R136*.2, R148*.1, R151*.1, U7.8 (V+), VR3*.1 (A); also elsewhere on the board
-B3*: R154*.2, R156*.2, U7.4 (V-); also elsewhere on the board
ACCENT_CH: Q8*.E, R16*.2; also elsewhere on the board
ACCENT_OH: Q7*.E, R17*.2; also elsewhere on the board
CH_OUT: J4.3, R172*.2
GND: C60*.-, C61*.-, C62*.-, C63*.-, C64*.2, C65*.2, C69*.2, C70*.2, M14.P$4 (C), M14.P$5 (C), M15.P$4 (C), M15.P$5 (C), M16.P$4 (C), M16.P$5 (C), Q3*.E, Q4*.E, Q21*.E, Q22*.E, Q23*.E, R7*.1, R8*.1, R13*.1, R130*.1, R139*.2, R143*.2, R145*.2, R146*.2, R152*.2, R155*.2, R157*.1, R158*.1, VR3*.P$4 (C), VR3*.P$5 (C), VR7*.P$4 (C), VR7*.P$5 (C), VR8*.P$4 (C), VR8*.P$5 (C); also elsewhere on the board
unnamed: C70*.1, D14*.C, Q30*.C
unnamed: C73*.2, Q31*.B, R155*.1
unnamed: C74*.2, R162*.1
unnamed: C80*.2, R160*.1
unnamed: C79*.1, C81*.-, R159*.1, R160*.2, U7.2 (-IN)
unnamed: C79*.2, R159*.2, R169*.1, U7.1 (OUT), VR7*.1 (A)
unnamed: C82*.1, C83*.-, R161*.1, R162*.2, U7.6 (-IN)
unnamed: C82*.2, R161*.2, R172*.1, U7.7 (OUT), VR8*.1 (A)
unnamed: Q21*.B, R130*.2, R131*.1
unnamed: Q29*.B, R140*.2
unnamed: C80*.1, Q26*.E, R147*.2, R156*.1
unnamed: C74*.1, Q31*.E, R153*.2, R154*.1
unnamed: C81*.+, VR7*.2 (S), VR7*.3 (E)
unnamed: R148*.2, R149*.1
unnamed: C64*.1, C66*.1, D13*.A, R144*.2
unnamed: C69*.1, C72*.1, D14*.A, R142*.2
unnamed: R150*.1, R151*.2
unnamed: R158*.2, U7.3 (+IN)
unnamed: R157*.2, U7.5 (+IN)
unnamed: R132*.2, VR3*.2 (S), VR3*.3 (E)
unnamed: C83*.+, VR8*.2 (S), VR8*.3 (E)
unnamed: Q4*.B, R2*.1, R7*.2
unnamed: Q8*.B, R11*.2, R16*.1
unnamed: Q4*.C, R11*.1
unnamed: Q8*.C, R13*.2, R141*.1
unnamed: Q3*.B, R1*.1, R8*.2
unnamed: Q7*.B, R12*.2, R17*.1
unnamed: Q3*.C, R12*.1
unnamed: Q7*.C, R131*.2, R135*.2
unnamed: Q24*.C, R137*.1
unnamed: Q24*.B, R135*.1
unnamed: C62*.+, Q24*.E, R134*.2, R139*.1, R140*.1
unnamed: Q22*.C, Q23*.C, R134*.1
unnamed: Q22*.B, R133*.1
unnamed: C60*.+, Q21*.C, R132*.1, R133*.2
unnamed: C61*.+, R136*.1, R137*.2, R138*.1
unnamed: Q28*.B, R141*.2
unnamed: Q28*.C, R138*.2
unnamed: Q23*.B, R173*.2
unnamed: C63*.+, Q28*.E, R142*.1, R173*.1
unnamed: Q29*.E, R143*.1, R144*.1
unnamed: Q30*.E, R152*.1
unnamed: Q27*.E, R145*.1
unnamed: C71*.2, Q30*.B, R150*.2
unnamed: C67*.2, Q27*.B, R149*.2
unnamed: C65*.1, D13*.C, Q27*.C
unnamed: C66*.2, C68*.1, R147*.1
unnamed: C72*.2, C73*.1, R153*.1
unnamed: C68*.2, Q26*.B, R146*.1
OH_OUT: J4.2, R169*.2
TO_HH: C67*.1, C71*.1; also elsewhere on the board
TRIG_CH: R2*.2; also elsewhere on the board
TRIG_OH: R1*.2; also elsewhere on the board

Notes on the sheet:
HitHat
